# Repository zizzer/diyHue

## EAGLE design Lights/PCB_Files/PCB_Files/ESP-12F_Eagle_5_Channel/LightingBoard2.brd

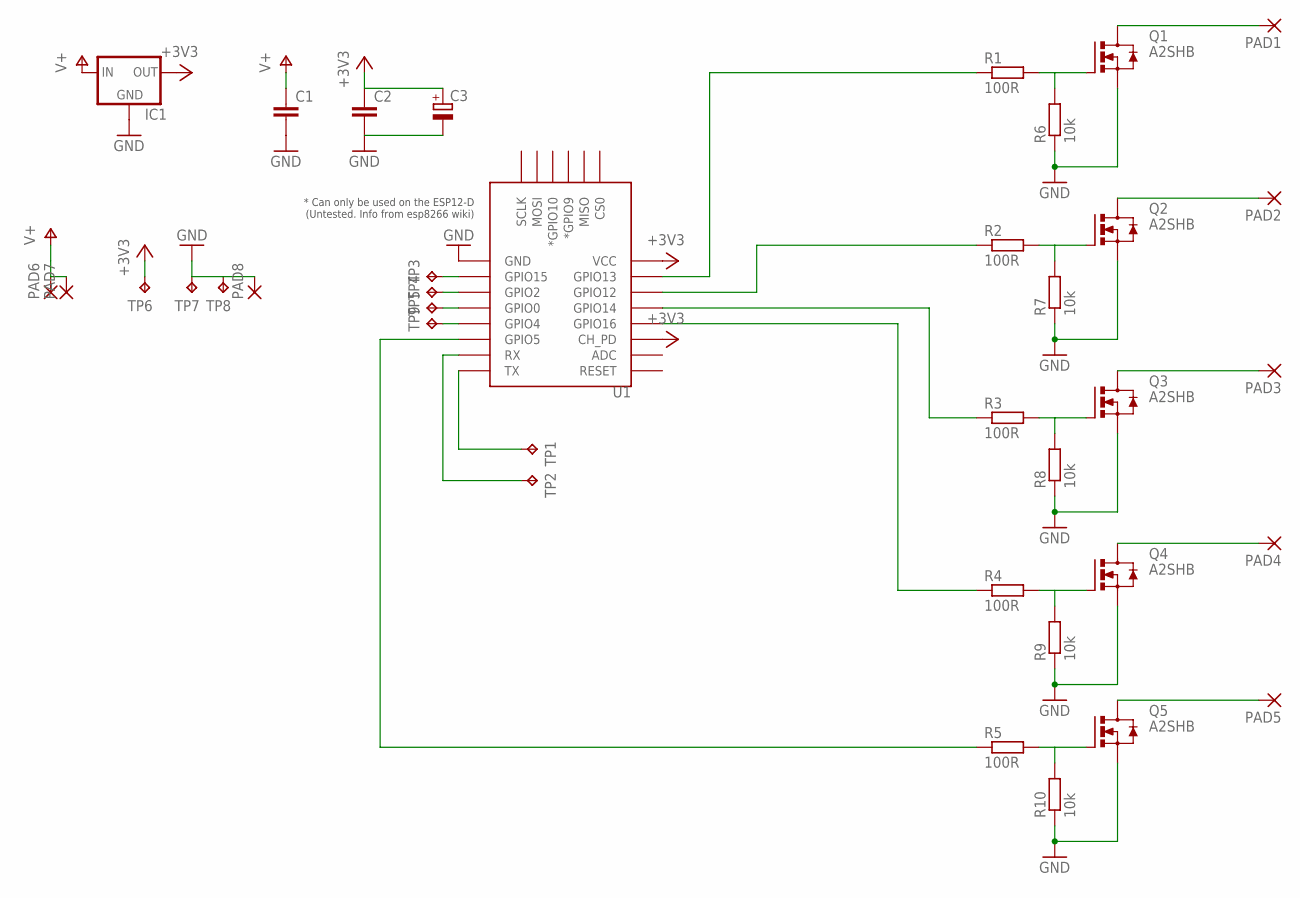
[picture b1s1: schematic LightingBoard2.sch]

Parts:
C1, C2: C-EUC0603; C0603
C3: CPOL-EU153CLV-0505; 153CLV-0505
IC1: LM1117; SOT223
PAD1, PAD2, PAD3, PAD4, PAD5, PAD6, PAD7, PAD8: SMD5; SMD2,54-5,08
Q1, Q2, Q3, Q4, Q5: A2SHB; SOT23
R1, R2, R3, R4, R5: 100R; R0603
R6, R7, R8, R9, R10: 10k; R0603
TP1, TP2: TPTP18R; TP18R
TP3, TP4, TP5, TP6, TP7, TP8, TP9: TPTP12SQ; TP12SQ
U1: ESP12ESMD; ESP12E-SMD

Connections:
+3V3: C2.1, C3.+, IC1.2 (OUT), TP6.TP, U1.CH_PD, U1.VCC
GND: C1.2, C2.2, C3.-, IC1.1 (GND), PAD8.1, Q1.2 (S), Q2.2 (S), Q3.2 (S), Q4.2 (S), Q5.2 (S), R6.1, R7.1, R8.1, R9.1, R10.1, TP7.TP, TP8.TP, U1.GND
unnamed: Q2.1 (G), R2.2, R7.2
unnamed: Q1.1 (G), R1.2, R6.2
unnamed: Q3.1 (G), R3.2, R8.2
unnamed: Q4.1 (G), R4.2, R9.2
unnamed: Q5.1 (G), R5.2, R10.2
unnamed: TP9.TP, U1.GPIO4
unnamed: R1.1, U1.GPIO13
unnamed: R2.1, U1.GPIO12
unnamed: R3.1, U1.GPIO14
unnamed: R4.1, U1.GPIO16
unnamed: R5.1, U1.GPIO5
unnamed: PAD5.1, Q5.3 (D)
unnamed: PAD4.1, Q4.3 (D)
unnamed: PAD3.1, Q3.3 (D)
unnamed: PAD2.1, Q2.3 (D)
unnamed: PAD1.1, Q1.3 (D)
unnamed: TP1.TP, U1.TXD0 (TX)
unnamed: TP2.TP, U1.RXD0 (RX)
unnamed: TP3.TP, U1.GPIO15
unnamed: TP4.TP, U1.GPIO2
unnamed: TP5.TP, U1.GPIO0
V+: C1.1, IC1.3 (IN), PAD6.1, PAD7.1

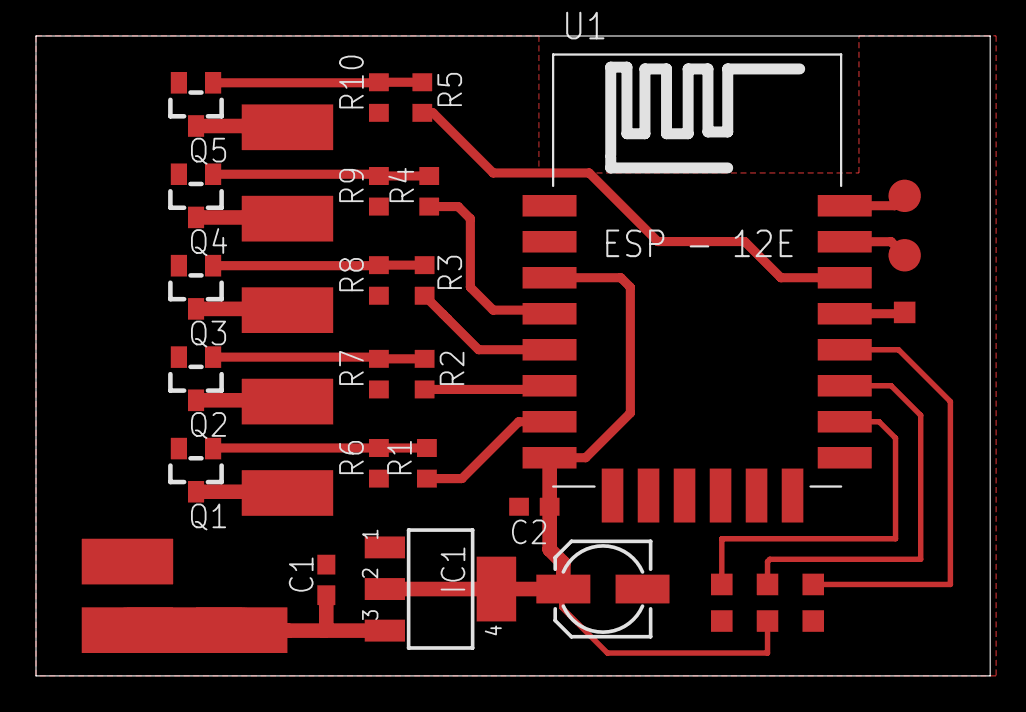
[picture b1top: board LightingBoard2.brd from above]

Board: 2 copper layers, 53.0 x 35.5 mm, 37 parts (0 on the bottom side), 24 nets.

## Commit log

2018-01-21 Fixed pwm include
    Script now compiles.
2018-01-21 Added 5ch board Eagle files
2018-01-21 Added schematic image
2018-02-03 Increased thickness of undersized tracks

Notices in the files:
parts and their libraries:
m-pad-2.1: License : GNU General Public License version 2 (see bottom)
